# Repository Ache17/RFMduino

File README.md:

# RFMduino
RFM69HCW / RFM95W extension board with oled display for arduino ( very small project needed for cansat testing and ground station )

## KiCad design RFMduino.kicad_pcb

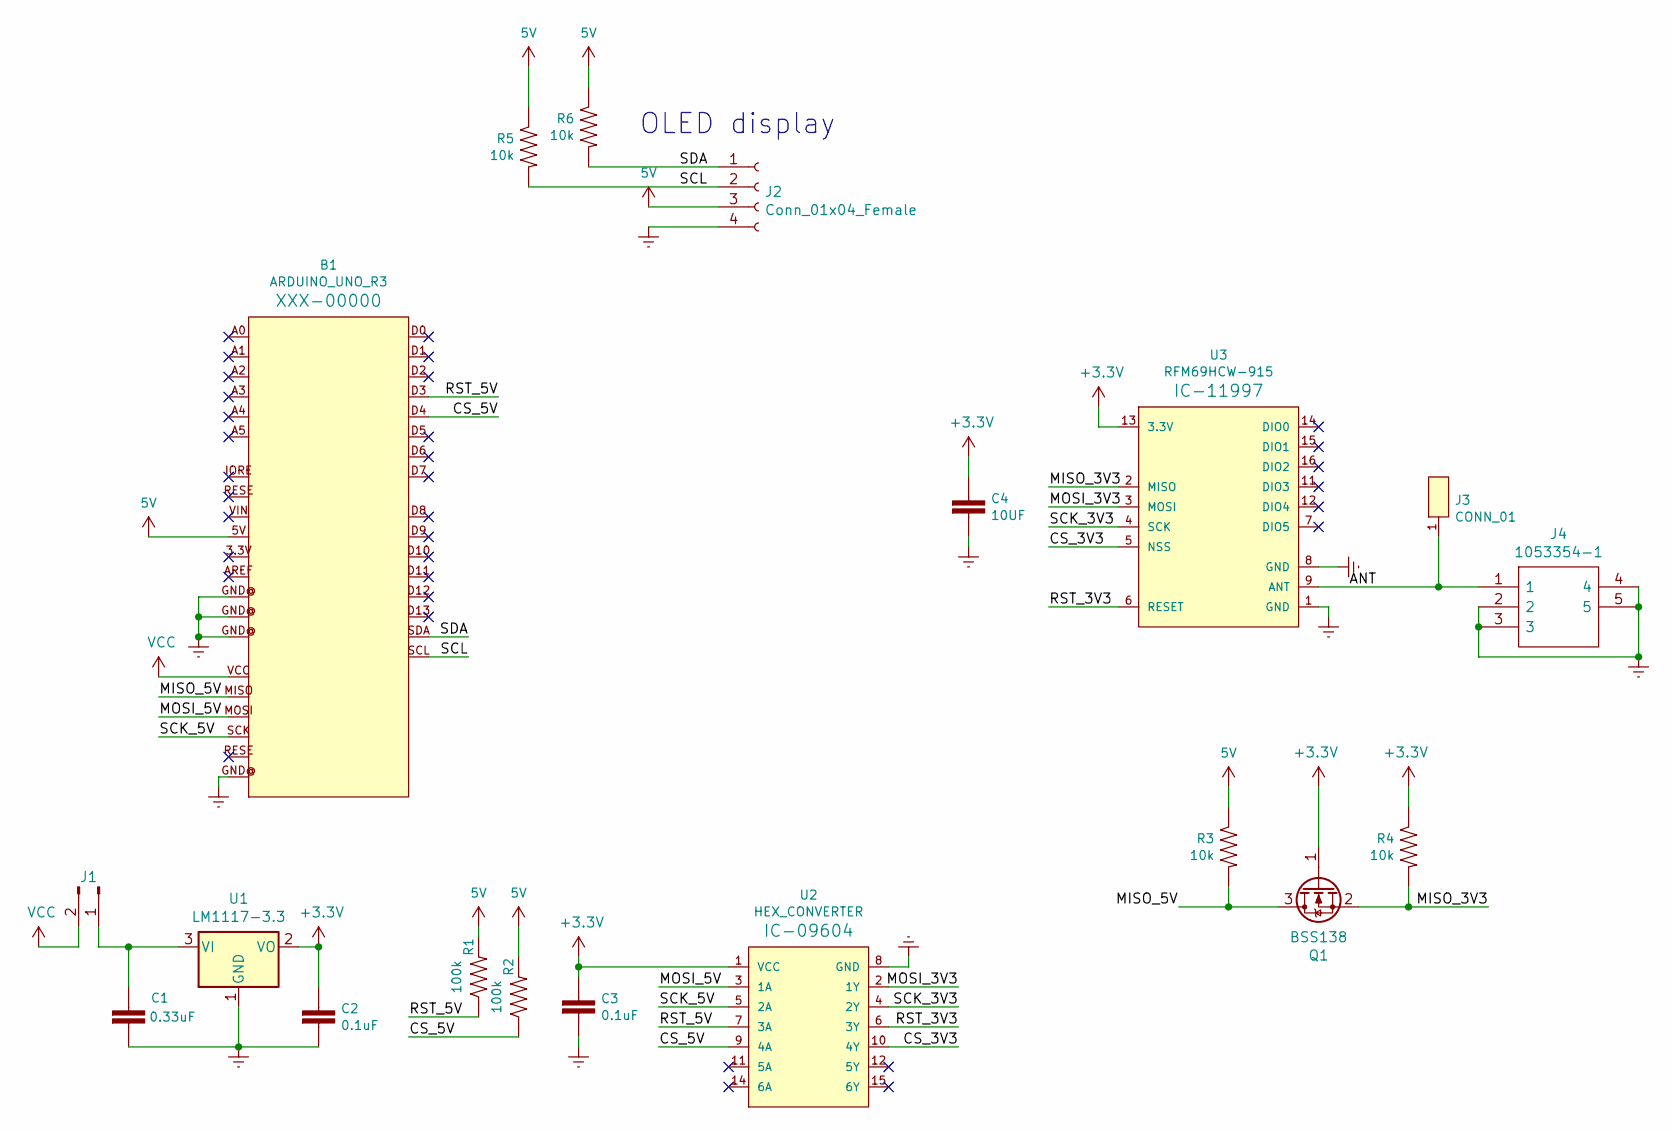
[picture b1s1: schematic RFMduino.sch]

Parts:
B1: ARDUINO_UNO_R3; ARDUINO_R3
C1: 0.33uF; C_0603_1608Metric
C2, C3: 0.1uF; C_0603_1608Metric
C4: 10UF; C_0603_1608Metric
J1: Conn_01x02_Male; 1X02
J2: Conn_01x04_Female; 1X04
J3: CONN_01; 1X01
J4: 1053354-1; 10533541; Manufacturer_Part_Number 1053354-1
Q1: BSS138; SOT-23
R1, R2: 100k; R_0603_1608Metric
R3, R4, R5, R6: 10k; R_0603_1608Metric
U1: LM1117-3.3; SOT230P700X180-4N
U2: HEX_CONVERTER; SO16
U3: RFM69HCW-915; RFM69HCW-XXXS2

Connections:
5V: B1.5V, J2.3, R1.2, R2.2, R3.1, R5.1, R6.1
+3V3: C2.1, C3.1, C4.1, Q1.1 (G), R4.1, U1.2 (VO), U2.1 (VCC), U3.13 (3.3V)
/ANT: J3.1, J4.1, U3.9 (ANT)
/CS_3V3: U2.10 (4Y), U3.5 (NSS)
/CS_5V: B1.D4, R2.1, U2.9 (4A)
/MISO_3V3: Q1.2 (S), R4.2, U3.2 (MISO)
/MISO_5V: B1.MISO, Q1.3 (D), R3.2
/MOSI_3V3: U2.2 (1Y), U3.3 (MOSI)
/MOSI_5V: B1.MOSI, U2.3 (1A)
/RST_3V3: U2.6 (3Y), U3.6 (RESET)
/RST_5V: B1.D3 (*D3), R1.1, U2.7 (3A)
/SCK_3V3: U2.4 (2Y), U3.4 (SCK)
/SCK_5V: B1.SCK, U2.5 (2A)
/SCL: B1.SCL, J2.2, R5.2
/SDA: B1.SDA, J2.1, R6.2
Earth: B1.GND@ (GND), C1.2, C2.2, C3.2, C4.2, J2.4, J4.2, J4.3, J4.4, J4.5, U1.1 (GND), U2.8 (GND), U3.1 (GND), U3.8 (GND), U3.10 (GND)
unnamed: C1.1, J1.1, U1.3 (VI)
VCC: B1.VCC, J1.2

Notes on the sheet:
OLED display

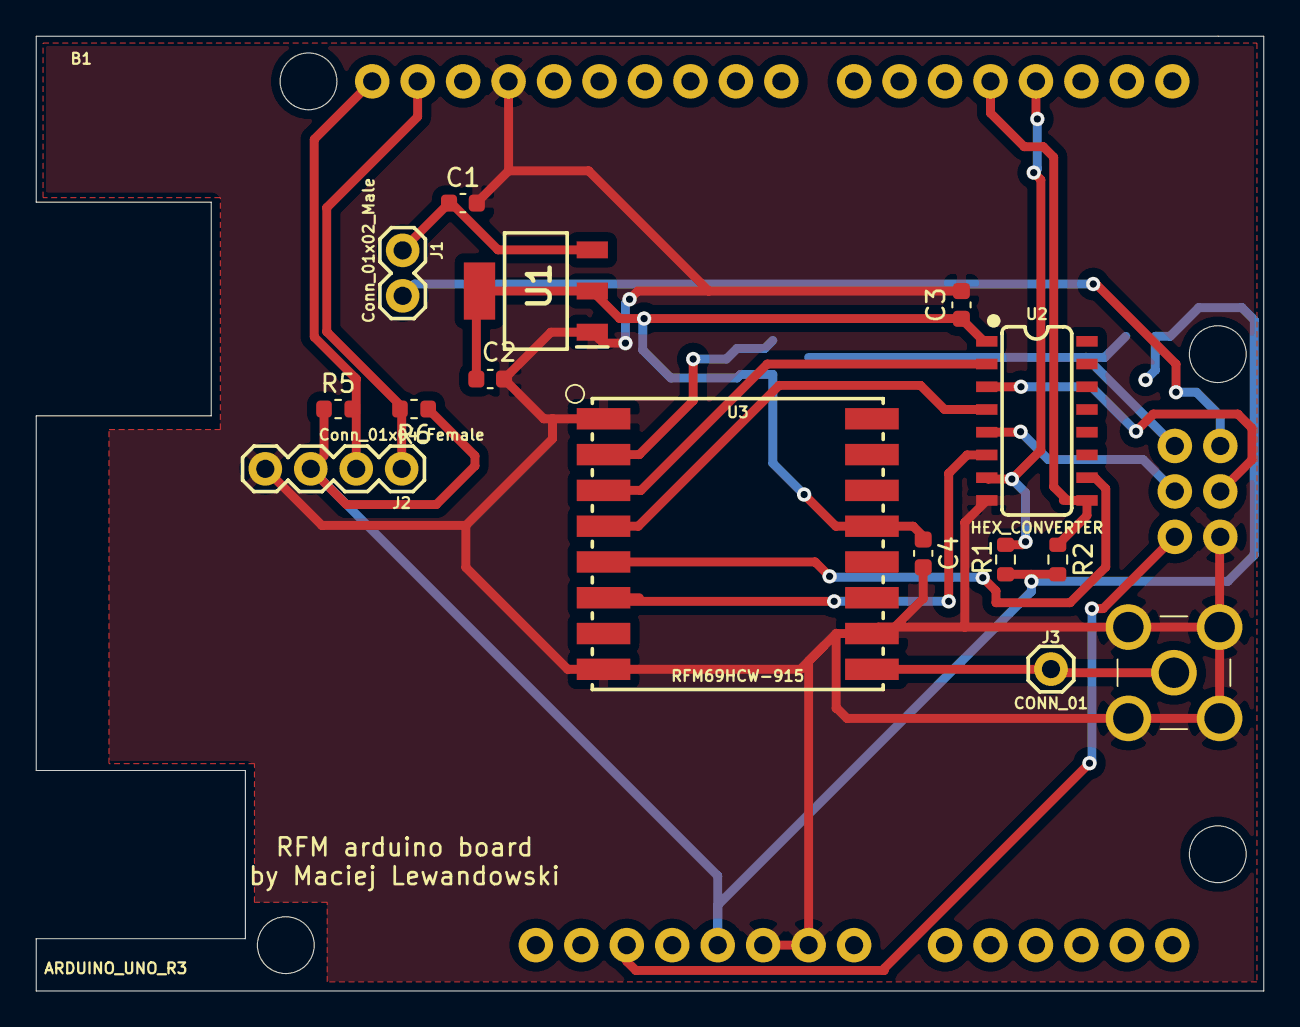
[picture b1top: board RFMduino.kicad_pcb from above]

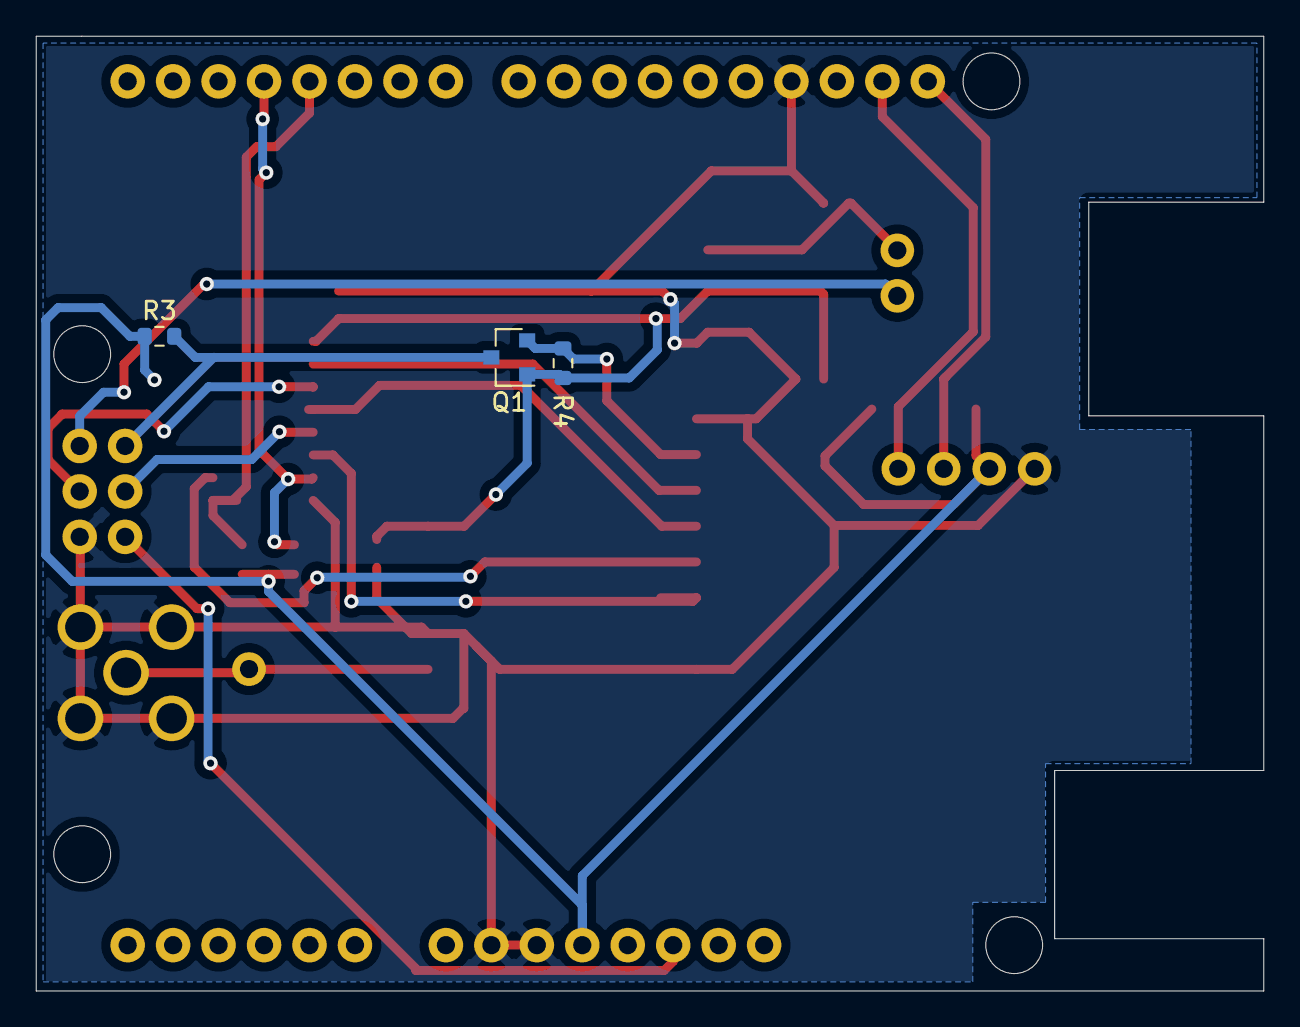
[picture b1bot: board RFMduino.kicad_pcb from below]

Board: 2 copper layers, 68.6 x 53.3 mm, 19 parts (3 on the bottom side), 18 nets.

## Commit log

2021-02-21 corrected pcb
